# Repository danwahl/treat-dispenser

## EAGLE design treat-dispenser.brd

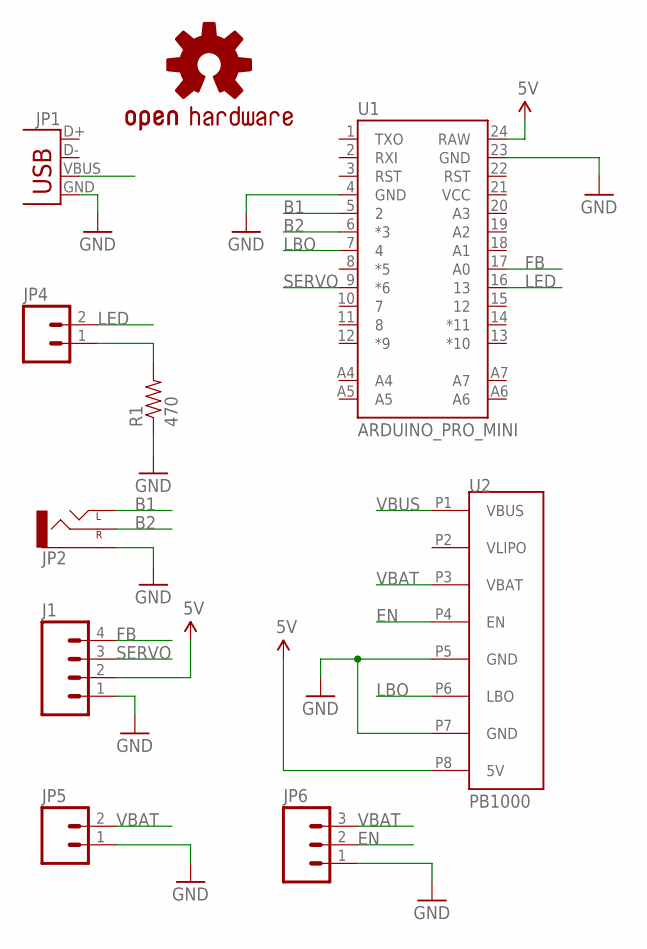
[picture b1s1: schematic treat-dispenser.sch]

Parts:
J1: M04PTH; 1X04
JP1: USB-MB-H
JP2: AUDIO-JACKPTH; AUDIO-JACK
JP4: M02PTH; 1X02
JP5: M02JST-PTH-2; JST-2-PTH
JP6: M03PTH; 1X03
LOGO1: OSHW-LOGOS; OSHW-LOGO-S
R1: 470; AXIAL-0.4
U1: ARDUINO_PRO_MINI
U2: PB1000

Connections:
5V: J1.2, U1.24 (RAW), U2.P8 (5V)
B1: JP2.TIP (LEFT), U1.5 (2)
B2: JP2.RING (RIGHT), U1.6 (*3)
EN: JP6.2, U2.P4 (EN)
FB: J1.4, U1.17 (A0)
GND: J1.1, JP1.GND, JP2.SLEEVE, JP5.1, JP6.1, R1.P$1 (1), U1.4 (GND), U1.23 (GND), U2.P5 (GND), U2.P7 (GND)
LBO: U1.7 (4), U2.P6 (LBO)
LED: JP4.2, U1.16 (13)
unnamed: JP4.1, R1.P$2 (2)
SERVO: J1.3, U1.9 (*6)
VBAT: JP5.2, JP6.3, U2.P3 (VBAT)
VBUS: JP1.VBUS, U2.P1 (VBUS)

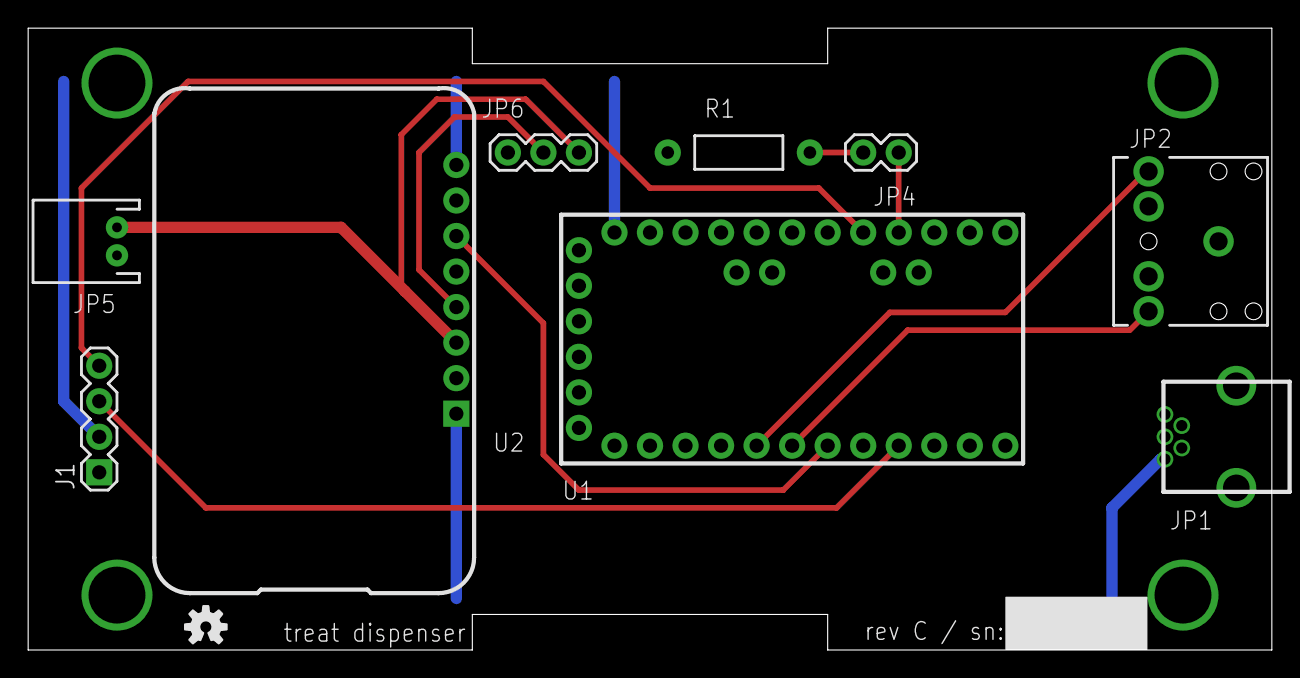
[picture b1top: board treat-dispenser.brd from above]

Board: 2 copper layers, 88.9 x 44.5 mm, 10 parts (0 on the bottom side), 12 nets.

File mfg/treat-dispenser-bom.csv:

"Qty";"Value";"Device";"Package";"Parts";"Description";"PN";
"1";"";"AUDIO-JACKPTH";"AUDIO-JACK";"JP3";"3.5mm Audio Jack";"CP1-3523N-ND";
"1";"";"M02PTH";"1X02";"JP7";"Standard 2-pin 0.1" header. Use with";"952-1311-ND";
"1";"";"M03PTH";"1X03";"JP5";"Header 3";"952-1312-ND";
"1";"";"USB-MB-H";"USB-MB-H";"JP4";"USB Connectors";"WM17115-ND";
"1";"470";"RESISTORPTH-1/4W";"AXIAL-0.4";"R13";"Resistor";"CF14JT470RCT-ND";
"1";"ARDUINO_PRO_MINI";"ARDUINO_PRO_MINI";"ARDUINO_PRO_MINI";"U$1";"";"1568-1055-ND";
"1";"PB1000";"PB1000";"PB1000";"U$2";"";"1528-1349-ND";

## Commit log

2015-09-04 fixed some routing issues, added part numbers
2015-09-05 minor fixes and part changes, added status led
2015-09-05 added optional sensor, cleaned up for mfg
2015-09-05 added part numbers for bom, manufacturing files
2015-09-06 fixed part names
2015-10-25 rev A initial commit
2015-11-16 rev A update with new board dxf
2015-11-16 mfg files update
2015-11-29 moved servo to clear path for battery connector
2015-11-29 output dxf for part placement in mechanical design
2015-12-03 adding prototype arduino code
2015-12-05 new software commit with low power enabled
2015-12-13 rev C update: - added dedicated battery connector - reversed led polarity - added enable switch - removed en connection to arduino - added status led and lbo to arduino code
2016-03-01 eagle and arduino update for servo with feedback sensor
2016-11-16 Cycle test code
2016-11-16 Removing and replacing treat_dispenser with new code
2016-11-16 New treat-dispenser code

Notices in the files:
parts and their libraries:
SparkFun-Connectors: Licensing: Creative Commons ShareAlike 4.0 International - https://creativecommons.org/licenses/by-sa/4.0
